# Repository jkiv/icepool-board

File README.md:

icepool-board
=============

KiCad 5 design files for the `icepool` project.

`icepool` is a FPGA cluster and development board.

Key features include,

- 16x headers for daughter boards.
- An FT2232H for USB communication and parallel FPGA flashing.
- One-to-many SPI interface for sending data from the PC to each daughter board.
- Daisy-chained SPI interface for passing data to and from the PC and each daughter board.
- A 6-pin ATX +12V power connector for use with conventional PC power supplies.

Currently, the project includes a daughter board design featuring a single [ice40hx8k-bg121](http://www.latticesemi.com/iCE40) FPGA with independent 1.2V LDO, 12MHz oscillator, and indicator LED.

## Dependencies

This project depends on the following KiCad libraries:

* [Digi-Key/digikey-kicad-library](https://github.com/Digi-Key/digikey-kicad-library)
* [jkiv/jkiv-kicad-library](https://github.com/jkiv/jkiv-kicad-library)

These repositories are set up as git submodules and can be cloned into `hardware/external/` using the following two commands:

    $ git submodule init
    $ git submodule update

## Drivers

See [jkiv/icepool-driver](https://github.com/jkiv/icepool-driver) project for a general-purpose Linux C library with Python3 bindings.

## Cores

* [jkiv/shapool-core](https://github.com/jkiv/shapool-core) - a SHA256d hashing core for cryptocurrency mining.

## Donate

Please consider supporting this project and others like it by donating:

* ☕: [ko-fi.com/jkiv_](https://ko-fi.com/jkiv_)
* ₿: `13zRrs1YDdooUN5WtfXRSDn8KnJdok4qG9`

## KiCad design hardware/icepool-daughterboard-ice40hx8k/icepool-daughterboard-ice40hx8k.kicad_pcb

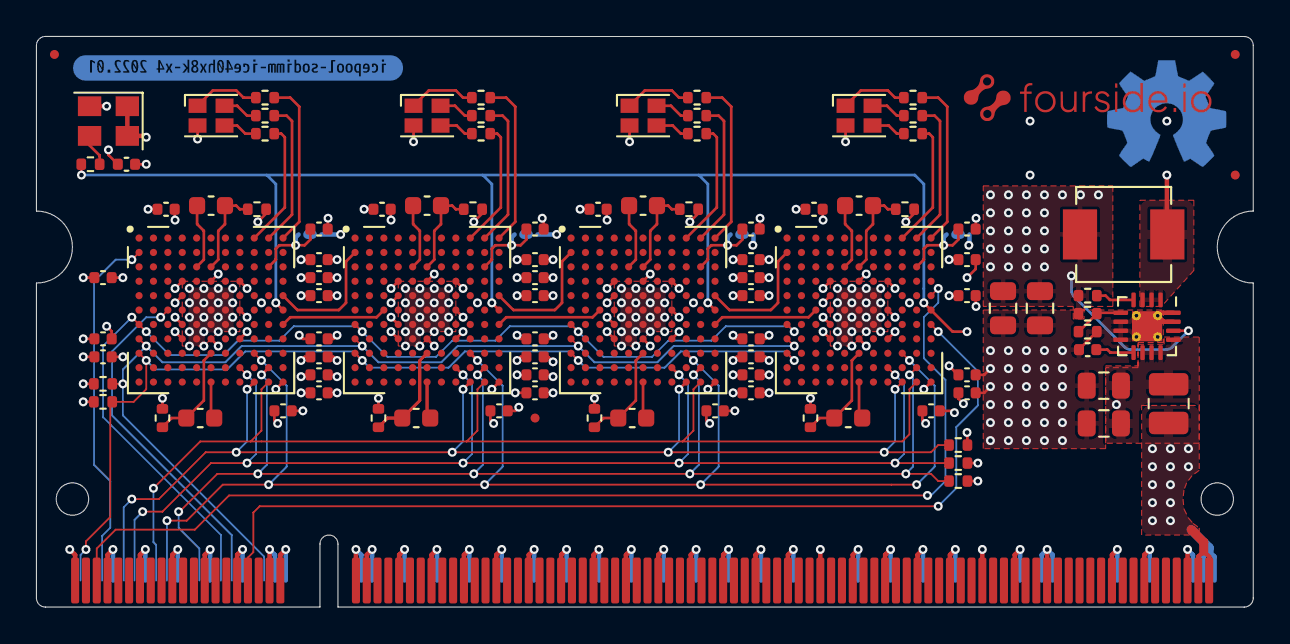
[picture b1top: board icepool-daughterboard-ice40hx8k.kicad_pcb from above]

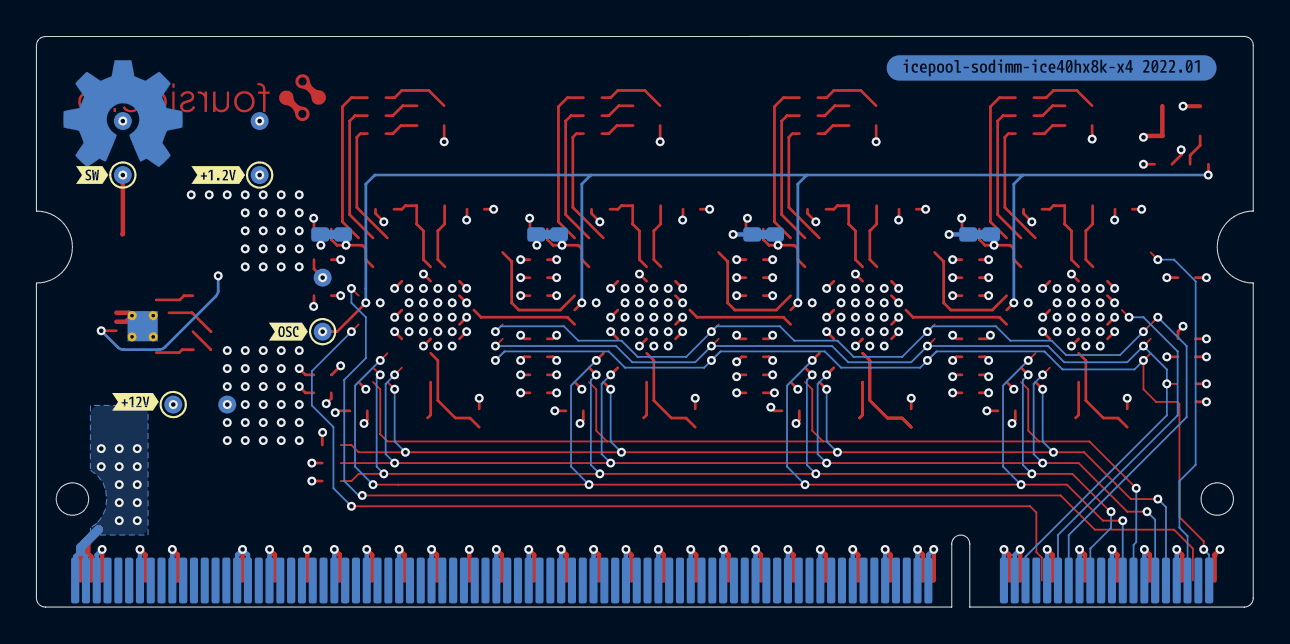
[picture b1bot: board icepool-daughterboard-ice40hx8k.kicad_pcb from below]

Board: 6 copper layers, 67.6 x 31.7 mm, 119 parts (19 on the bottom side), 73 nets.

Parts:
C1, C53: DNP; C_0805_2012Metric
C2, C4: 22u; C_0805_2012Metric
C3: 3.3n; C_0402_1005Metric
C5, C6, C7, C8, C9, C10, C11, C12, C14, C15, C17, C18, C19, C20, C21, C22, C23, C24, C26, C27, C29, C30, C31, C32, C33, C34, C35, C36, C38, C39, C41, C42, C43, C44, C45, C46, C47, C48, C50, C51: 0.1u; C_0402_1005Metric
C13, C16, C25, C28, C37, C40, C49, C52: 10u; C_0603_1608Metric
C54: 22u; C_0402_1005Metric
D1, D2, D3, D4: ACT_LED; LED_Cree-PLCC4_2x2mm_CW
FID1, FID2, FID3, FID4: Fiducial; Fiducial_0.5mm_Mask1mm
J1: SODIMM-200_Split; SODIMM-200-DDR2-PCB
JP1, JP2, JP3, JP4: CUT_2V5; J_Small_NC
L1: FB; L_1008_2520Metric
L2: 2.2u; L_Vishay_IHLP-2020
OSHW1: Logo_Open_Hardware_Small; OSHW-Symbol_6.7x6mm_Copper
R1: 100k; R_0402_1005Metric
R2: 75k; R_0402_1005Metric
R3: 150k; R_0402_1005Metric
R4: 22R; R_0402_1005Metric
R5, R6, R15, R16, R25, R26, R35, R36: 100R; R_0402_1005Metric
R7, R8, R10, R12, R14: 10k; R_0402_1005Metric
R9, R11, R13, R19, R21, R23, R29, R31, R33, R39, R41, R43: 1k; R_0402_1005Metric
TP1: SW_1v2; TestPoint_Pad_D1.0mm
TP2, TP4, TP6, TP8: GND; TestPoint_Pad_D1.0mm
TP3: +12V; TestPoint_Pad_D1.0mm
TP5: +1v2; TestPoint_Pad_D1.0mm
TP7: OSC_CORE; TestPoint_Pad_D1.0mm
U0, U1, U2, U3: iCE40HX8K-BG121(121-Ball_caBGA); BGA-121_11x11_9.0x9.0mm
U4: TPS62140; VQFN-16-1EP_3x3mm_P0.5mm_EP1.68x1.68mm_ThermalVias
X1: ASEM1-12.000MHZ; Oscillator_SMD_Abracon_ASE-4Pin_3.2x2.5mm
kibuzzard-62B88C8F: G***; kibuzzard-62B88C8F
kibuzzard-62B88CC0: G***; kibuzzard-62B88CC0
kibuzzard-62B88D1E: G***; kibuzzard-62B88D1E
kibuzzard-62B88D7B: G***; kibuzzard-62B88D7B
kibuzzard-62C46161: G***; kibuzzard-62C46161
kibuzzard-62C46174: G***; kibuzzard-62C46174

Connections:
12V_IN: J1.197, J1.198, J1.199, J1.200, L1.1
+1V2: C4.1, C6.2, C9.2, C11.2, C14.2, C18.2, C21.2, C23.2, C26.2, C30.2, C33.2, C35.2, C38.2, C42.2, C45.2, C47.2, C50.2, C53.1, L2.2, R1.1, R2.1, R5.2, R6.2, R15.2, R16.2, R25.2, R26.2, R35.2, R36.2, TP5.1, U0.D4 (VCC), U0.D8 (VCC), U0.H4 (VCC), U0.H8 (VCC), U1.D4 (VCC), U1.D8 (VCC), U1.H4 (VCC), U1.H8 (VCC), U2.D4 (VCC), U2.D8 (VCC), U2.H4 (VCC), U2.H8 (VCC), U3.D4 (VCC), U3.D8 (VCC), U3.H4 (VCC), U3.H8 (VCC), U4.14 (VOS)
+3V3: C5.2, C7.2, C10.2, C12.2, C15.2, C17.2, C19.2, C22.2, C24.2, C27.2, C29.2, C31.2, C34.2, C36.2, C39.2, C41.2, C43.2, C46.2, C48.2, C51.2, C54.2, D1.4 (A), D2.4 (A), D3.4 (A), D4.4 (A), J1.39, J1.40, J1.41, J1.42, JP1.1, JP2.1, JP3.1, JP4.1, R7.1, R8.1, R10.1, R12.1, U0.D6 (VCCIO_0), U0.E4 (VCCIO_3), U0.F8 (VCCIO_1), U0.G4 (VCCIO_3), U0.H6 (VCCIO_2), U0.L11 (VCC_SPI), U1.D6 (VCCIO_0), U1.E4 (VCCIO_3), U1.F8 (VCCIO_1), U1.G4 (VCCIO_3), U1.H6 (VCCIO_2), U1.L11 (VCC_SPI), U2.D6 (VCCIO_0), U2.E4 (VCCIO_3), U2.F8 (VCCIO_1), U2.G4 (VCCIO_3), U2.H6 (VCCIO_2), U2.L11 (VCC_SPI), U3.D6 (VCCIO_0), U3.E4 (VCCIO_3), U3.F8 (VCCIO_1), U3.G4 (VCCIO_3), U3.H6 (VCCIO_2), U3.L11 (VCC_SPI), X1.1 (EN), X1.4 (Vdd)
+12V: C1.2, C2.2, L1.2, TP3.1, U4.10 (AVIN), U4.11 (PVIN), U4.12 (PVIN), U4.13 (EN)
/CDONE: J1.12, R10.2, U0.K8 (CDONE), U1.K8 (CDONE), U3.K8 (CDONE)
/CRESET_B: J1.10, R7.2, U0.L9 (CRESET_B), U1.L9 (CRESET_B), U2.L9 (CRESET_B), U3.L9 (CRESET_B)
/OSC_CORE: R4.1, TP7.1, U0.F11 (GBIN3/IOR_140/PIO1_11), U1.F11 (GBIN3/IOR_140/PIO1_11), U2.F11 (GBIN3/IOR_140/PIO1_11), U3.F11 (GBIN3/IOR_140/PIO1_11)
/SCK0: J1.16, U0.L10 (SCK/IOB_107/PIO2_21), U1.L10 (SCK/IOB_107/PIO2_21), U2.L10 (SCK/IOB_107/PIO2_21), U3.L10 (SCK/IOB_107/PIO2_21)
/SCK1: J1.28, U0.G1 (GBIN6/IOL_14A/PIO3_16), U1.G1 (GBIN6/IOL_14A/PIO3_16), U2.G1 (GBIN6/IOL_14A/PIO3_16), U3.G1 (GBIN6/IOL_14A/PIO3_16)
/SDI0: J1.18, U0.J9 (SDI/IOB_106/PIO2_20), U1.J9 (SDI/IOB_106/PIO2_20), U2.J9 (SDI/IOB_106/PIO2_20), U3.J9 (SDI/IOB_106/PIO2_20)
/SDI1: J1.30, U0.F3 (GBIN7/IOL_13B/PIO3_15)
/SDO1: J1.33, U3.G11 (IOR_129/PIO1_08)
/SW_1v2: L2.1, TP1.1, U4.1 (SW), U4.2 (SW), U4.3 (SW)
/ice40-hx8k 1/GNDPLL0: C25.2, U1.L6 (GNDPLL0)
/ice40-hx8k 1/GNDPLL1: C28.2, U1.C5 (GNDPLL1)
/ice40-hx8k 1/SDI1: U0.G11 (IOR_129/PIO1_08), U1.F3 (GBIN7/IOL_13B/PIO3_15)
/ice40-hx8k 1/SDO1: U1.G11 (IOR_129/PIO1_08), U2.F3 (GBIN7/IOL_13B/PIO3_15)
/ice40-hx8k 1/VCCPLL0: C25.1, R15.1, U1.J6 (VCCPLL0)
/ice40-hx8k 1/VCCPLL1: C28.1, R16.1, U1.C6 (VCCPLL1)
/ice40-hx8k 1/VPP_2V5: C20.2, JP2.2, U1.C10 (VPP_2V5)
/ice40-hx8k 1/~ACT_B: R23.1, U1.A9 (IOT_178/PIO0_05)
/ice40-hx8k 1/~ACT_G: R21.1, U1.A10 (IOT_170/PIO0_01)
/ice40-hx8k 1/~ACT_R: R19.1, U1.A11 (IOT_168/PIO0_00)
/ice40-hx8k 1/~READY_IN: U1.E11 (IOR_148/PIO1_16), U2.B1 (IOL_2A/PIO3_00)
/ice40-hx8k 1/~READY_OUT: U0.E11 (IOR_148/PIO1_16), U1.B1 (IOL_2A/PIO3_00)
/ice40-hx8k 2/GNDPLL0: C37.2, U2.L6 (GNDPLL0)
/ice40-hx8k 2/GNDPLL1: C40.2, U2.C5 (GNDPLL1)
/ice40-hx8k 2/SDO1: U2.G11 (IOR_129/PIO1_08), U3.F3 (GBIN7/IOL_13B/PIO3_15)
/ice40-hx8k 2/VCCPLL0: C37.1, R25.1, U2.J6 (VCCPLL0)
/ice40-hx8k 2/VCCPLL1: C40.1, R26.1, U2.C6 (VCCPLL1)
/ice40-hx8k 2/VPP_2V5: C32.2, JP3.2, U2.C10 (VPP_2V5)
/ice40-hx8k 2/~ACT_B: R33.1, U2.A9 (IOT_178/PIO0_05)
/ice40-hx8k 2/~ACT_G: R31.1, U2.A10 (IOT_170/PIO0_01)
/ice40-hx8k 2/~ACT_R: R29.1, U2.A11 (IOT_168/PIO0_00)
/ice40-hx8k 2/~READY_IN: U2.E11 (IOR_148/PIO1_16), U3.B1 (IOL_2A/PIO3_00)
/ice40-hx8k 3/GNDPLL0: C49.2, U3.L6 (GNDPLL0)
/ice40-hx8k 3/GNDPLL1: C52.2, U3.C5 (GNDPLL1)
/ice40-hx8k 3/VCCPLL0: C49.1, R35.1, U3.J6 (VCCPLL0)
/ice40-hx8k 3/VCCPLL1: C52.1, R36.1, U3.C6 (VCCPLL1)
/ice40-hx8k 3/VPP_2V5: C44.2, JP4.2, U3.C10 (VPP_2V5)
/ice40-hx8k 3/~ACT_B: R43.1, U3.A9 (IOT_178/PIO0_05)
/ice40-hx8k 3/~ACT_G: R41.1, U3.A10 (IOT_170/PIO0_01)
/ice40-hx8k 3/~ACT_R: R39.1, U3.A11 (IOT_168/PIO0_00)
/ice40hx8k 0/GNDPLL0: C13.2, U0.L6 (GNDPLL0)
/ice40hx8k 0/GNDPLL1: C16.2, U0.C5 (GNDPLL1)
/ice40hx8k 0/VCCPLL0: C13.1, R5.1, U0.J6 (VCCPLL0)
/ice40hx8k 0/VCCPLL1: C16.1, R6.1, U0.C6 (VCCPLL1)
/ice40hx8k 0/VPP_2V5: C8.2, JP1.2, U0.C10 (VPP_2V5)
/ice40hx8k 0/~ACT_B: R13.1, U0.A9 (IOT_178/PIO0_05)
/ice40hx8k 0/~ACT_G: R11.1, U0.A10 (IOT_170/PIO0_01)
/ice40hx8k 0/~ACT_R: R9.1, U0.A11 (IOT_168/PIO0_00)
/~CS0: J1.24, R14.2, U0.K10 (SS/IOB_108/PIO2_22), U1.K10 (SS/IOB_108/PIO2_22), U2.K10 (SS/IOB_108/PIO2_22), U3.K10 (SS/IOB_108/PIO2_22)
/~CS1: J1.36, R12.2, U0.H1 (IOL_18A/PIO3_20), U1.H1 (IOL_18A/PIO3_20), U2.H1 (IOL_18A/PIO3_20), U3.H1 (IOL_18A/PIO3_20)
/~READY_IN: J1.5, U3.E11 (IOR_148/PIO1_16)
/~READY_OUT: J1.6, U0.B1 (IOL_2A/PIO3_00)
/~RESET: J1.2, R8.2, U0.J1 (IOL_23A/PIO3_22), U1.J1 (IOL_23A/PIO3_22), U2.J1 (IOL_23A/PIO3_22), U3.J1 (IOL_23A/PIO3_22)
GND: C1.1, C2.1, C3.2, C4.2, C5.1, C6.1, C7.1, C8.1, C9.1, C10.1, C11.1, C12.1, C14.1, C15.1, C17.1, C18.1, C19.1, C20.1, C21.1, C22.1, C23.1, C24.1, C26.1, C27.1, C29.1, C30.1, C31.1, C32.1, C33.1, C34.1, C35.1, C36.1, C38.1, C39.1, C41.1, C42.1, C43.1, C44.1, C45.1, C46.1, C47.1, C48.1, C50.1, C51.1, C53.2, C54.1, J1.1, J1.7, J1.8, J1.13, J1.14, J1.19, J1.20, J1.25, J1.26, J1.31, J1.32, J1.37, J1.38, J1.43, J1.44, J1.49, J1.50, J1.55, J1.56, J1.61, J1.62, J1.67, J1.68, J1.73, J1.74, J1.79, J1.80, J1.85, J1.86, J1.91, J1.92, J1.97, J1.98, J1.103, J1.104, J1.109, J1.110, J1.115, J1.116, J1.121, J1.122, J1.127, J1.133, J1.134, J1.139, J1.140, J1.145, J1.146, J1.151, J1.152, J1.157, J1.163, J1.164, J1.168, J1.169, J1.170, J1.181, J1.182, J1.187, J1.188, J1.195, J1.196, R3.2, R14.1, TP2.1, TP4.1, TP6.1, TP8.1, U0.E5 (GND), U0.E6 (GND), U0.E7 (GND), U0.F5 (GND), U0.F6 (GND), U0.F7 (GND), U0.G5 (GND), U0.G6 (GND), U0.G7 (GND), U0.H5 (GND), U1.E5 (GND), U1.E6 (GND), U1.E7 (GND), U1.F5 (GND), U1.F6 (GND), U1.F7 (GND), U1.G5 (GND), U1.G6 (GND), U1.G7 (GND), U1.H5 (GND), U2.E5 (GND), U2.E6 (GND), U2.E7 (GND), U2.F5 (GND), U2.F6 (GND), U2.F7 (GND), U2.G5 (GND), U2.G6 (GND), U2.G7 (GND), U2.H5 (GND), U3.E5 (GND), U3.E6 (GND), U3.E7 (GND), U3.F5 (GND), U3.F6 (GND), U3.F7 (GND), U3.G5 (GND), U3.G6 (GND), U3.G7 (GND), U3.H5 (GND), U4.6 (AGND), U4.7 (FSW), U4.8 (DEF), U4.15 (PGND), U4.16 (PGND), U4.17 (EP), X1.2 (GND)
unnamed: C3.1, U4.9 (SS/TR)
unnamed: D1.1 (RK), R9.2
unnamed: D1.2 (GK), R11.2
unnamed: D1.3 (BK), R13.2
unnamed: D2.1 (RK), R19.2
unnamed: D2.2 (GK), R21.2
unnamed: D2.3 (BK), R23.2
unnamed: D3.1 (RK), R29.2
unnamed: D3.2 (GK), R31.2
unnamed: D3.3 (BK), R33.2
unnamed: D4.1 (RK), R39.2
unnamed: D4.2 (GK), R41.2
unnamed: D4.3 (BK), R43.2
unnamed: R1.2, U4.4 (PG)
unnamed: R2.2, R3.1, U4.5 (FB)
unnamed: R4.2, X1.3 (OUT)

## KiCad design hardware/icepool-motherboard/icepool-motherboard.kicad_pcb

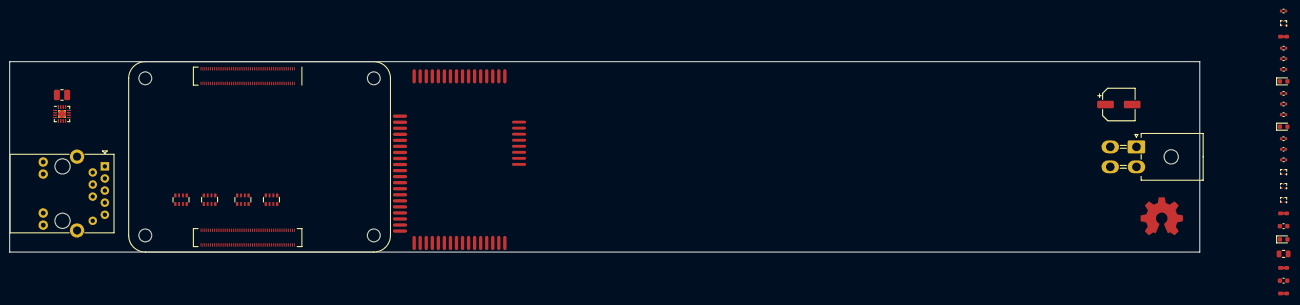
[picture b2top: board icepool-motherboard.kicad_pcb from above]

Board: 2 copper layers, 250.0 x 40.0 mm, 40 parts (1 on the bottom side), 57 nets, no tracks yet.

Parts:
C1: 22u; C_0805_2012Metric
C2: 47u; CP_Elec_6.3x5.9
C3: 10u; C_0603_1608Metric
C4: 3.3n; C_0402_1005Metric
C5: 22u; C_0603_1608Metric
D1: PI_ACT; LED_0603_1608Metric
D3: 5V; LED_0603_1608Metric
D4: 3v3; LED_0603_1608Metric
D6, D7, D8, D9: TPD2EUSB30DRTR; SOT-3
J1: microSD; microSD_HC_Molex_104031-0811
J2: PWR; Molex_Mini-Fit_Jr_5569-04A2_2x02_P4.20mm_Horizontal
J3: Abracon_ARJM11-502; RJ45_Abracon_ARJP11A-MA_Horizontal
J4: S; PinHeader_1x20_P1.27mm_Vertical
J5: E; PinHeader_1x16_P1.27mm_Vertical
J6: W; PinHeader_1x16_P1.27mm_Vertical
J7: N; PinHeader_1x08_P1.27mm_Vertical
JP1, JP4: ~WL_nDisable; J_Small_NC
JP2: ~BT_nDisable; J_Small_NC
JP3: EEPROM_nWP; J_Small_NC
L2: 2.2u; L_1008_2520Metric
OSHW1: Logo_Open_Hardware_Small; OSHW-Symbol_8.9x8mm_Copper
R1, R3, R4, R8: 220R; R_0402_1005Metric
R2, R10, R11: 1k0; R_0402_1005Metric
R6: 330R; R_0402_1005Metric
R12: 100k; R_0402_1005Metric
RN1, RN2, RN3, RN4: 22R; R_Array_Convex_4x0603
U1: CM4; Raspberry-Pi-4-Compute-Module
U2: TPS62140; VQFN-16-1EP_3x3mm_P0.5mm_EP1.68x1.68mm_ThermalVias

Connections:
+1V8: U1.88, U1.90
+3V3: C1.1, D1.2, D4.2, J1.4, J3.11, J3.13, JP4.2, U1.78, U1.84, U1.86
+5V: C5.1, D3.2, L2.2, R12.1, U1.77, U1.79, U1.81, U1.83, U1.85, U1.87, U2.14
/5V_SW: L2.1, U2.1, U2.2, U2.3
/CIPO1: RN4.3, U1.26
/COPI0: RN1.3, RN3.3, U1.44
/COPI1: RN2.2, U1.27
/ETH_TD1+: D6.1, J3.1, U1.12
/ETH_TD1-: D6.2, J3.2, U1.10
/ETH_TD2+: D7.1, J3.3, U1.4
/ETH_TD2-: D7.2, J3.4, U1.6
/ETH_TD3+: D8.1, J3.7, U1.11
/ETH_TD3-: D8.2, U1.9
/ETH_TD4+: D9.1, J3.9, U1.3
/ETH_TD4-: D9.2, J3.10, U1.5
/FPGA_CDONE: J4.16, U1.46
/FPGA_CRESETB: RN2.4, U1.37
/FPGA_~READY~: J4.2, RN4.1, U1.58
/FPGA_~RESET~: RN1.4, RN3.4, U1.56
/Nodes/COPI0: J4.12, RN1.6
/Nodes/COPI1: J4.6, RN2.7
/Nodes/CRESETB: J4.18, RN2.5
/Nodes/SCK0: J4.10, RN1.8
/Nodes/SCK1: J4.4, RN2.8
/Nodes/~CS0: J4.14, RN1.7
/Nodes/~CS1: J4.8, RN2.6
/Nodes/~RESET: J4.20, RN1.5
/PI_GLOBAL_EN: R4.2, U1.99
/PI_LED_nACT: R1.2, U1.21
/SCK0: RN1.1, RN3.1, U1.38
/SCK1: RN2.1, U1.25
/SD_CLK: J1.5, U1.57
/SD_CMD: J1.3, U1.62
/SD_DAT0: J1.7, U1.63
/SD_DAT1: J1.8, U1.67
/SD_DAT2: J1.1, U1.69
/SD_DAT3: J1.2, U1.61
/~CS0: RN1.2, RN3.2, U1.39
/~CS1: RN2.3, U1.49
/~ETH_LEDL: R11.2, U1.17
/~ETH_LEDR: R10.2, U1.19
GND: C1.2, C2.2, C3.1, C4.2, C5.2, D6.3, D7.3, D8.3, D9.3, J1.6, J1.9, J4.1, J4.3, J4.5, J4.7, J4.9, J4.11, J4.13, J4.15, J4.17, J4.19, J5.1, J5.2, J5.3, J5.4, J5.5, J5.6, J5.7, J5.8, J5.9, J5.11, J5.13, J5.15, J6.1, J6.2, J6.3, J6.4, J6.5, J6.6, J6.7, J6.8, J6.9, J6.10, J6.11, J6.12, J7.2, J7.4, J7.6, J7.8, JP1.1, JP2.1, JP3.1, R2.1, R6.2, R8.2, RN3.5, RN3.6, RN3.7, RN3.8, RN4.5, RN4.6, RN4.7, RN4.8, U1.1, U1.2, U1.7, U1.8, U1.13, U1.14, U1.22, U1.23, U1.32, U1.33, U1.42, U1.43, U1.52, U1.53, U1.59, U1.60, U1.65, U1.66, U1.71, U1.74, U1.98, U1.107, U1.108, U1.113, U1.114, U1.119, U1.120, U1.125, U1.126, U1.131, U1.132, U1.137, U1.138, U1.144, U1.150, U1.155, U1.156, U1.161, U1.162, U1.167, U1.168, U1.173, U1.174, U1.179, U1.180, U1.185, U1.186, U1.191, U1.192, U1.197, U1.198, U2.5, U2.6, U2.7, U2.8, U2.15, U2.16, U2.17
unnamed: C4.1, U2.9
unnamed: D1.1, R1.1
unnamed: D3.1, R6.1
unnamed: D4.1, R8.1
unnamed: J2.1, J2.2
unnamed: J2.3, J2.4
unnamed: J3.5, J3.6
unnamed: J3.12, R11.1
unnamed: J3.14, R10.1
unnamed: JP1.2, U1.89
unnamed: JP2.2, U1.91
unnamed: JP3.2, U1.20
unnamed: JP4.1, U1.73
unnamed: R12.2, U2.4
VBUS: C2.1, C3.2, J6.13, J6.14, J6.15, J6.16, U2.10, U2.11, U2.12, U2.13

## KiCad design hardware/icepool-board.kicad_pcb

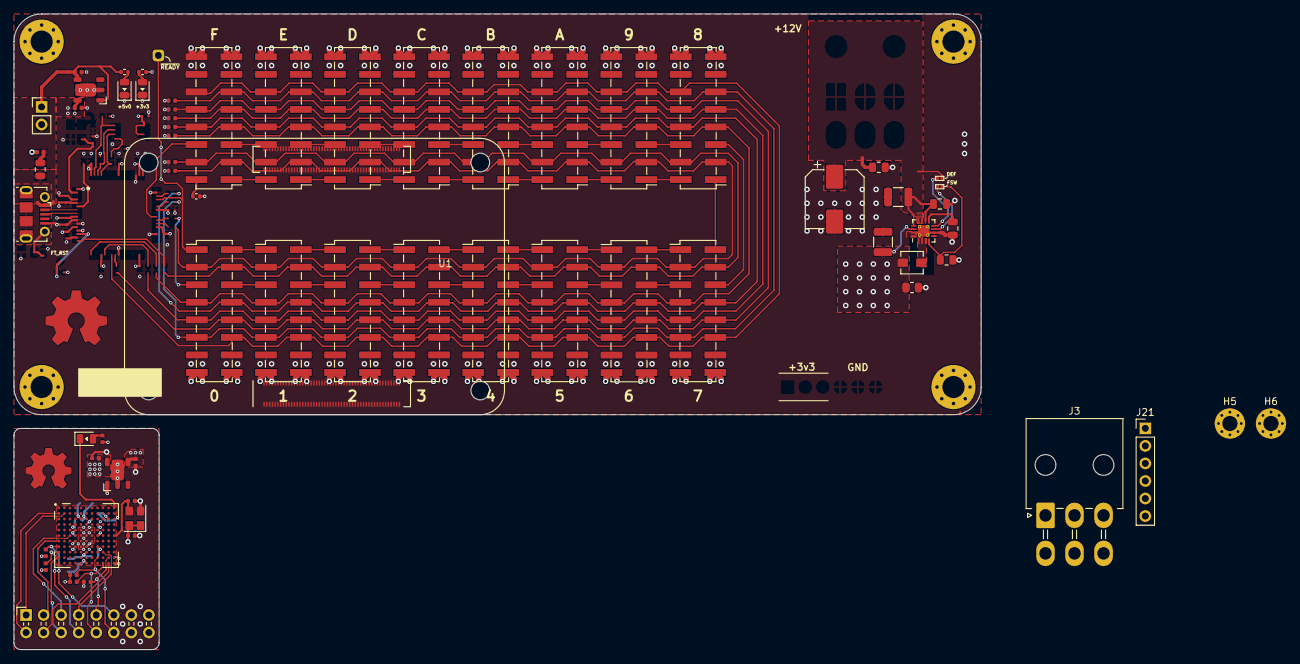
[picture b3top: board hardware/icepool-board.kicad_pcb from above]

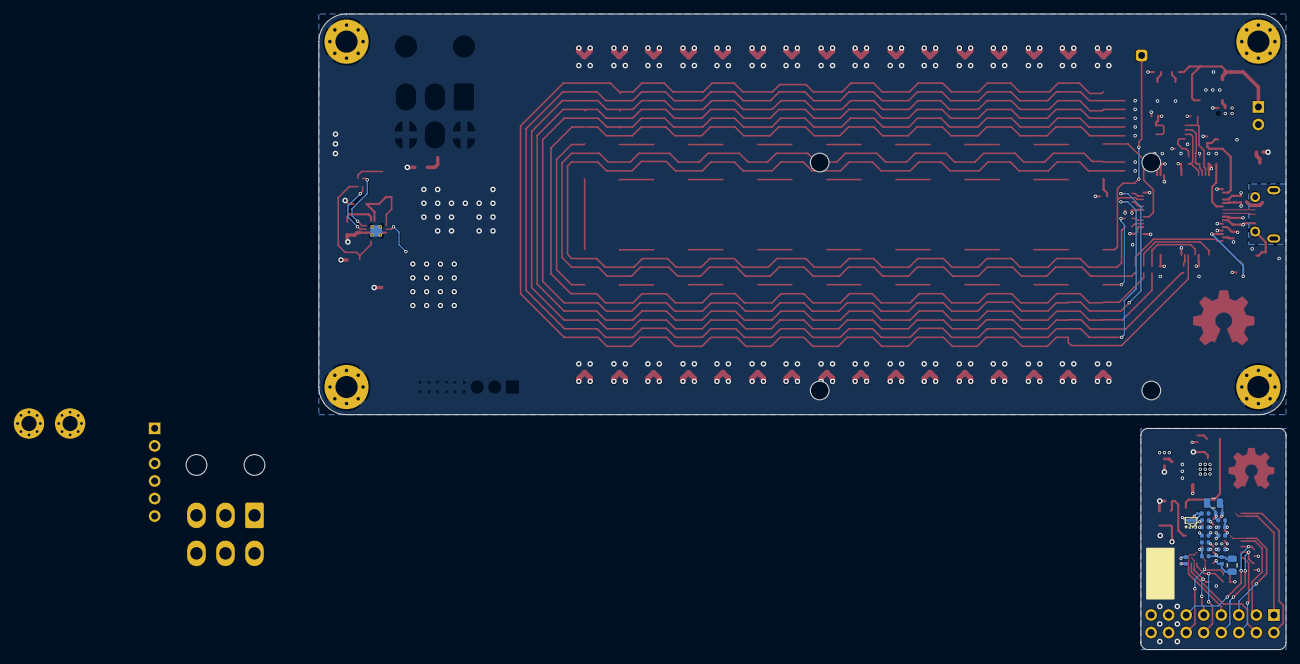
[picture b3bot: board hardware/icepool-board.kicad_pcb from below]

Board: 4 copper layers, 140.0 x 92.0 mm, 91 parts (17 on the bottom side), 76 nets.

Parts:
C7, C11, C12, C21, C22: 4.7u; C_0402_1005Metric
C15: 47u; CP_Elec_8x10
C16, C23, C24, C25, C26, C27, C28, C29, C30, C32, C33, C34, C36: 0.1u; C_0402_1005Metric
C17: DNP; C_0402_1005Metric
C31, C35: 10u; C_0805_2012Metric
C37: 10u; C_1210_3225Metric
C38: 3.3u; C_0805_2012Metric
C39: 0.1u; C_0805_2012Metric
C41: 22u; C_1210_3225Metric
D1: VBUS_LED; LED_0805_2012Metric
D2: LED_IND; LED_0805_2012Metric
D3: PWRLED; LED_0805_2012Metric
FB1: FB; L_0805_2012Metric
H1, H2, H3, H4: M3_PHT; MountingHole_3.2mm_M3_Pad_Via
H5, H6: MountingHole_Pad; MountingHole_2.2mm_M2_Pad_Via
J1: USB_B_Micro; USB_Micro-B_Molex-105017-0001
J2: USE_VBUS_5V; PinHeader_1x02_P2.54mm_Vertical
J3: PCIe_6pin; Molex_Mini-Fit_Jr_5569-06A2_2x03_P4.20mm_Horizontal
J4, J5, J6, J7, J8, J9, J10, J11, J12, J13, J14, J15, J16, J17, J18, J19: Conn_02x08_Odd_Even; PinHeader_2x08_P2.54mm_Vertical_SMD
J20: Conn_02x08_Odd_Even; PinSocket_2x08_P2.54mm_Horizontal
J21: PWR_ALT; PinHeader_1x06_P2.54mm_Vertical
J22: ~READY; PinHeader_1x01_P2.54mm_Vertical
JP1: CUT_2V5; SolderJumper-2_P1.3mm_Bridged_Pad1.0x1.5mm
JP2, JP3: FSW; J_NO_0201_0603Metric
L1: 2.2u; L_Vishay_IHLP-1212
OSHW1: Logo_Open_Hardware_Small; OSHW-Symbol_6.7x6mm_Copper
OSHW2: Logo_Open_Hardware_Small; OSHW-Symbol_8.9x8mm_Copper
R1, R25, R36: 4k7; R_0402_1005Metric
R10, R24, R26, R27, R28, R29, R30: DNP; R_0402_1005Metric
R14: 1k; R_0402_1005Metric
R15, R16: 100R; R_0402_1005Metric
R17, R18, R19, R20, R31: 10k; R_0402_1005Metric
R21, R22, R23: 100k; R_0805_2012Metric
U1: Compute_Module_4_Connectors; Raspberry-Pi-4-Compute-Module
U2, U7: AP7361C_SOT-89-5; SOT89-5
U3: TPS62132; VQFN-16-1EP_3x3mm_P0.5mm_EP1.68x1.68mm_ThermalVias
U8: iCE40HX8K-BG121(121-Ball_caBGA); BGA-121_11x11_9.0x9.0mm
X2: ASEM1-12.000MHZ; Oscillator_SMD_Abracon_ASE-4Pin_3.2x2.5mm

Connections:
+1V2: C22.1, C24.2, C27.2, C29.2, C33.2, R15.2, R16.2, U7.5, U8.D4, U8.D8, U8.H4, U8.H8
+3V3: C12.1, C16.2, C21.1, C23.2, C25.2, C28.2, C30.2, C34.2, C41.1, J4.15, J4.16, J5.15, J5.16, J6.15, J6.16, J7.15, J7.16, J8.15, J8.16, J9.15, J9.16, J10.15, J10.16, J11.15, J11.16, J12.15, J12.16, J13.15, J13.16, J14.15, J14.16, J15.15, J15.16, J16.15, J16.16, J17.15, J17.16, J18.15, J18.16, J19.15, J19.16, J20.15, J20.16, J21.1, J21.2, J21.3, JP1.1, L1.2, R14.2, R18.1, R19.1, R20.1, R22.1, R23.1, R25.1, R31.1, U2.5, U3.14, U7.1, U7.4, U8.D6, U8.E4, U8.F8, U8.G4, U8.H6, U8.L11, X2.1, X2.4
+5V: C11.1, J2.1, R1.1, U2.1, U2.4
+12V: C15.1, C37.1, C39.1, J3.1, J3.2, J3.3, JP3.1, R21.1, U3.10, U3.11, U3.12, U3.13
/ice40hx8k-daughter-board/CDONE: J20.12, R20.2, U8.K8
/ice40hx8k-daughter-board/CLK_FPGA: C17.2, U8.F11, X2.3
/ice40hx8k-daughter-board/CRESET_B: J20.10, R18.2, U8.L9
/ice40hx8k-daughter-board/SCK0: J20.4, U8.L10
/ice40hx8k-daughter-board/SCK1: J20.3, U8.G1
/ice40hx8k-daughter-board/SDI0: J20.7, U8.J9
/ice40hx8k-daughter-board/SDI1: J20.5, U8.F3
/ice40hx8k-daughter-board/SDO1: J20.6, U8.K1
/ice40hx8k-daughter-board/ice40-hx8k-bg121/GNDPLL0: C31.2, C32.2, U8.L6
/ice40hx8k-daughter-board/ice40-hx8k-bg121/GNDPLL1: C35.2, C36.2, U8.C5
/ice40hx8k-daughter-board/ice40-hx8k-bg121/VCCPLL0: C31.1, C32.1, R15.1, U8.J6
/ice40hx8k-daughter-board/ice40-hx8k-bg121/VCCPLL1: C35.1, C36.1, R16.1, U8.C6
/ice40hx8k-daughter-board/ice40-hx8k-bg121/VPP_2V5: C26.2, JP1.2, U8.C10
/ice40hx8k-daughter-board/~CS0: J20.9, R17.2, U8.K10
/ice40hx8k-daughter-board/~CS1: J20.11, R31.2, U8.H1
/ice40hx8k-daughter-board/~LED: D2.1, U8.A11
/ice40hx8k-daughter-board/~READY_IN: J20.2, U8.B1
/ice40hx8k-daughter-board/~READY_OUT: J20.1, U8.B2
/ice40hx8k-daughter-board/~RESET: J20.8, R19.2, U8.J1
/icepool-motherboard/12V-3.3V Buck/DEF: JP3.2, U3.8
/icepool-motherboard/12V-3.3V Buck/FSW: JP2.2, U3.7
/icepool-motherboard/12V-3.3V Buck/PG: JP2.1, R22.2, U3.4
/icepool-motherboard/12V-3.3V Buck/SW: L1.1, U3.1, U3.2, U3.3
/icepool-motherboard/CDONE: J4.12, J5.12, J6.12, J7.12, J8.12, J9.12, J10.12, J11.12, J12.12, J13.12, J14.12, J15.12, J16.12, J17.12, J18.12, J19.12
/icepool-motherboard/COPI0: J4.7, J5.7, J6.7, J7.7, J8.7, J9.7, J10.7, J11.7, J12.7, J13.7, J14.7, J15.7, J16.7, J17.7, J18.7, J19.7, R24.2
/icepool-motherboard/CRESET_B: J4.10, J5.10, J6.10, J7.10, J8.10, J9.10, J10.10, J11.10, J12.10, J13.10, J14.10, J15.10, J16.10, J17.10, J18.10, J19.10, R30.2
/icepool-motherboard/SCK0: J4.4, J5.4, J6.4, J7.4, J8.4, J9.4, J10.4, J11.4, J12.4, J13.4, J14.4, J15.4, J16.4, J17.4, J18.4, J19.4, R10.2
/icepool-motherboard/SCK1: J4.3, J5.3, J6.3, J7.3, J8.3, J9.3, J10.3, J11.3, J12.3, J13.3, J14.3, J15.3, J16.3, J17.3, J18.3, J19.3, R27.2
/icepool-motherboard/SDO1_0: J4.6, J5.5
/icepool-motherboard/SDO1_1: J5.6, J6.5
/icepool-motherboard/SDO1_2: J6.6, J7.5
/icepool-motherboard/SDO1_3: J7.6, J8.5
/icepool-motherboard/SDO1_4: J8.6, J9.5
/icepool-motherboard/SDO1_5: J9.6, J10.5
/icepool-motherboard/SDO1_6: J10.6, J11.5
/icepool-motherboard/SDO1_7: J11.6, J12.5
/icepool-motherboard/SDO1_8: J12.6, J13.5
/icepool-motherboard/SDO1_9: J13.6, J14.5
/icepool-motherboard/SDO1_10: J14.6, J15.5
/icepool-motherboard/SDO1_11: J15.6, J16.5
/icepool-motherboard/SDO1_12: J16.6, J17.5
/icepool-motherboard/SDO1_13: J17.6, J18.5
/icepool-motherboard/SDO1_14: J18.6, J19.5
/icepool-motherboard/USB_D+: J1.3, U1.105
/icepool-motherboard/USB_D-: J1.2, U1.103
/icepool-motherboard/VBUS: C7.1, FB1.1, J2.2
/icepool-motherboard/~CS0: J4.9, J5.9, J6.9, J7.9, J8.9, J9.9, J10.9, J11.9, J12.9, J13.9, J14.9, J15.9, J16.9, J17.9, J18.9, J19.9, R26.2
/icepool-motherboard/~CS1: J4.11, J5.11, J6.11, J7.11, J8.11, J9.11, J10.11, J11.11, J12.11, J13.11, J14.11, J15.11, J16.11, J17.11, J18.11, J19.11, R28.2
/icepool-motherboard/~READY: J4.1, J22.1
/icepool-motherboard/~READY_0: J4.2, J5.1
/icepool-motherboard/~READY_1: J5.2, J6.1
/icepool-motherboard/~READY_2: J6.2, J7.1
/icepool-motherboard/~READY_3: J7.2, J8.1
/icepool-motherboard/~READY_4: J8.2, J9.1
/icepool-motherboard/~READY_5: J9.2, J10.1
/icepool-motherboard/~READY_6: J10.2, J11.1
/icepool-motherboard/~READY_7: J11.2, J12.1
/icepool-motherboard/~READY_8: J12.2, J13.1
/icepool-motherboard/~READY_9: J13.2, J14.1
/icepool-motherboard/~READY_10: J14.2, J15.1
/icepool-motherboard/~READY_11: J15.2, J16.1
/icepool-motherboard/~READY_12: J16.2, J17.1
/icepool-motherboard/~READY_13: J17.2, J18.1
/icepool-motherboard/~READY_14: J18.2, J19.1
/icepool-motherboard/~READY_15: J19.2, R36.2
/icepool-motherboard/~RESET: J4.8, J5.8, J6.8, J7.8, J8.8, J9.8, J10.8, J11.8, J12.8, J13.8, J14.8, J15.8, J16.8, J17.8, J18.8, J19.8, R29.2
GND: C7.2, C11.2, C12.2, C15.2, C16.1, C17.1, C21.2, C22.2, C23.1, C24.1, C25.1, C26.1, C27.1, C28.1, C29.1, C30.1, C33.1, C34.1, C37.2, C38.2, C39.2, C41.2, D1.1, D3.1, H1.1, H2.1, H3.1, H4.1, H5.1, H6.1, J1.5, J3.4, J3.6, J4.13, J4.14, J5.13, J5.14, J6.13, J6.14, J7.13, J7.14, J8.13, J8.14, J9.13, J9.14, J10.13, J10.14, J11.13, J11.14, J12.13, J12.14, J13.13, J13.14, J14.13, J14.14, J15.13, J15.14, J16.13, J16.14, J17.13, J17.14, J18.13, J18.14, J19.13, J19.14, J20.13, J20.14, J21.4, J21.5, J21.6, R10.1, R17.1, R21.2, R23.2, R24.1, R26.1, R27.1, R28.1, R29.1, R30.1, R36.1, U1.1, U1.2, U1.7, U1.8, U1.13, U1.14, U1.22, U1.23, U1.32, U1.33, U1.42, U1.43, U1.52, U1.53, U1.59, U1.60, U1.65, U1.66, U1.71, U1.74, U1.98, U1.107, U1.108, U1.113, U1.114, U1.119, U1.120, U1.125, U1.126, U1.131, U1.132, U1.137, U1.138, U1.144, U1.150, U1.155, U1.156, U1.161, U1.162, U1.167, U1.168, U1.173, U1.174, U1.179, U1.180, U1.185, U1.186, U1.191, U1.192, U1.197, U1.198, U2.2, U3.5, U3.6, U3.15, U3.16, U3.17, U7.2, U8.E5, U8.E6, U8.E7, U8.F5, U8.F6, U8.F7, U8.G5, U8.G6, U8.G7, U8.H5, X2.2
unnamed: C38.1, U3.9
unnamed: D1.2, R1.2
unnamed: D2.2, R14.1
unnamed: D3.2, R25.2
unnamed: FB1.2, J1.1

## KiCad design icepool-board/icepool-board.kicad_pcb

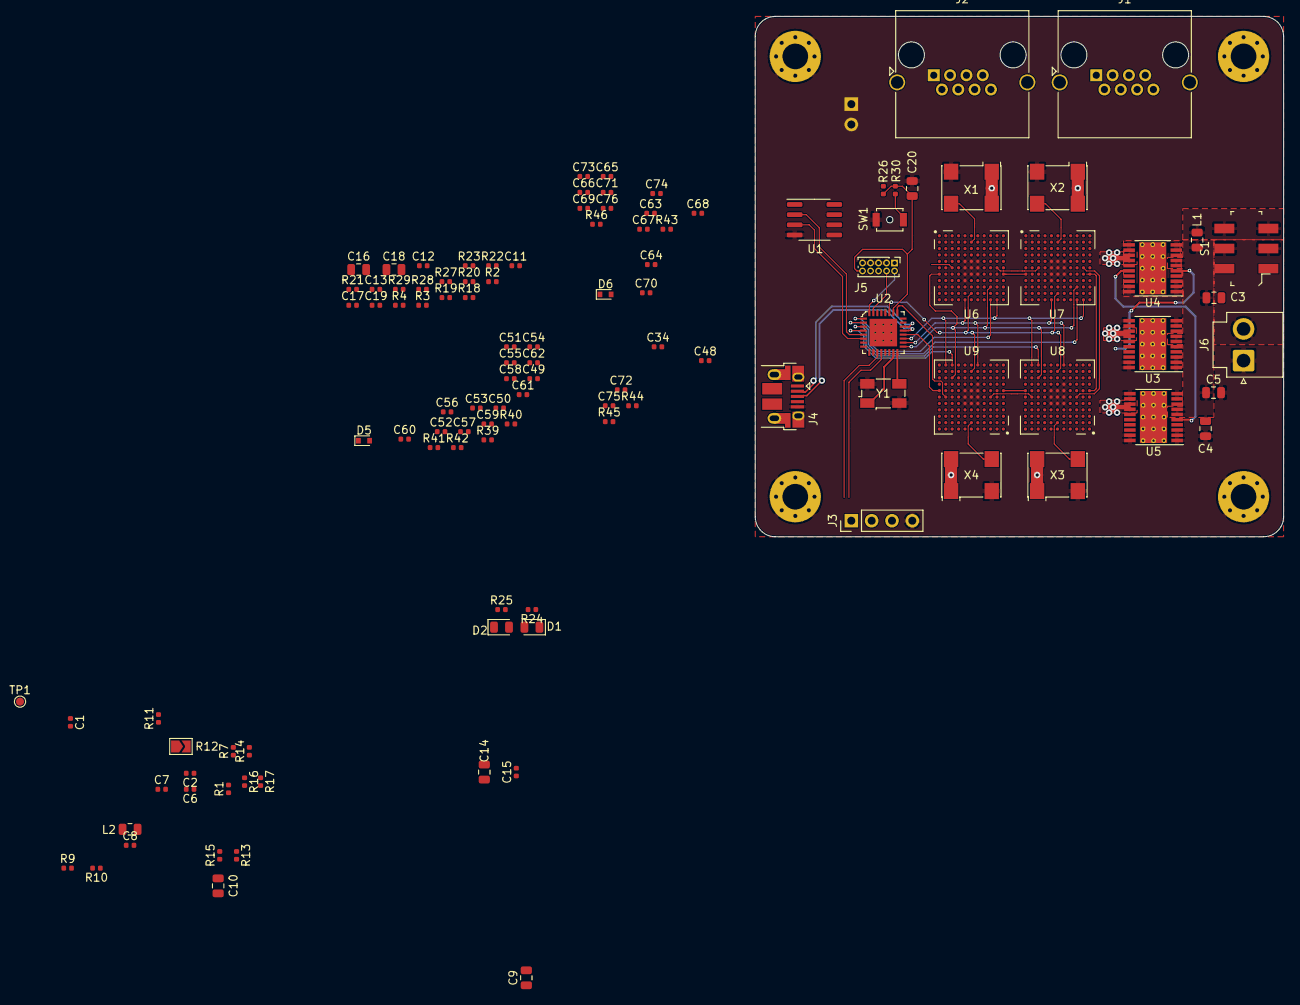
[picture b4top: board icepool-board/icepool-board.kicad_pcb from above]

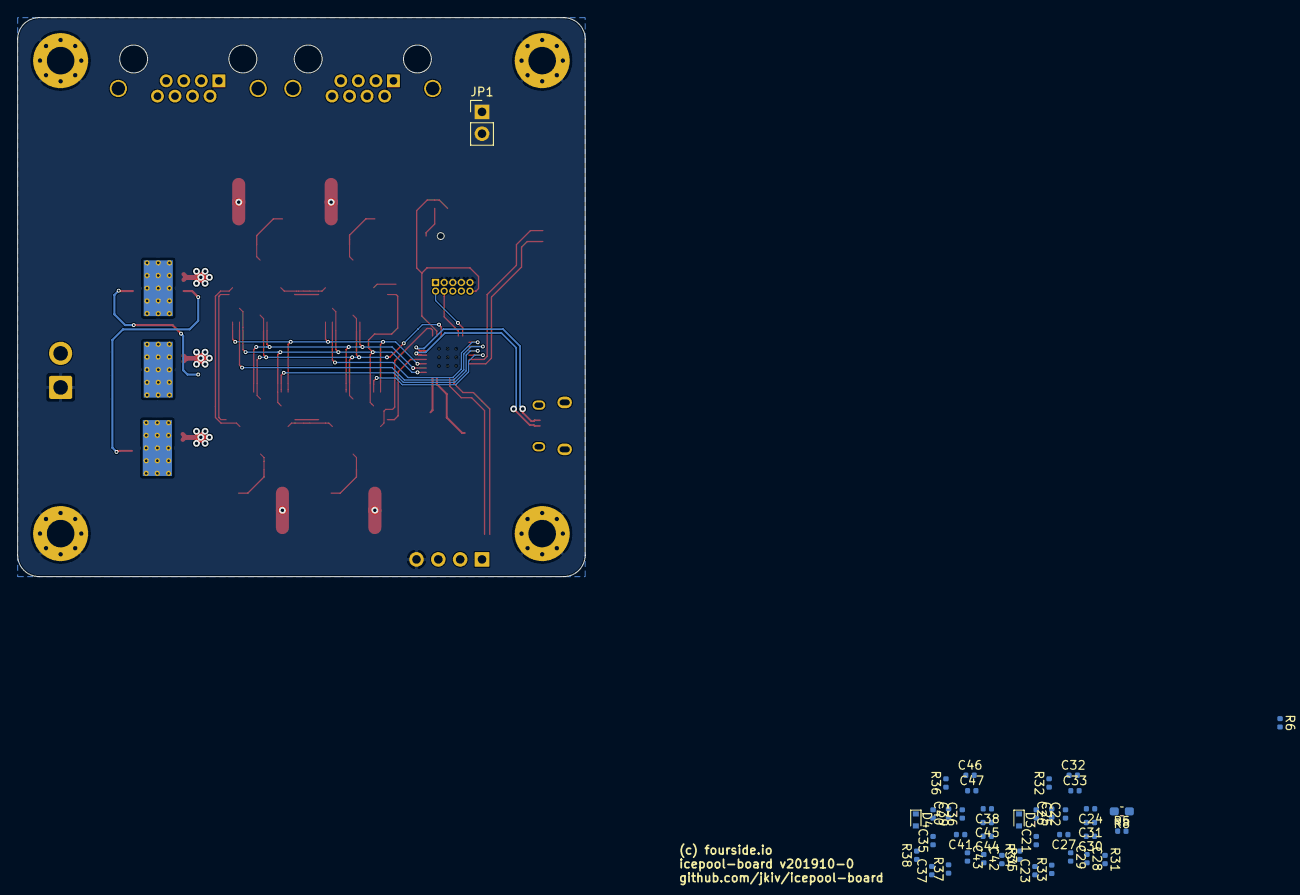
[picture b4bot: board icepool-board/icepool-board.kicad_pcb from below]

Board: 4 copper layers, 66.0 x 65.0 mm, 158 parts (40 on the bottom side), 85 nets.

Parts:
C1, C6, C7, C8, C11, C12, C13, C15, C17, C19, C21, C22, C23, C24, C25, C26, C27, C29, C30, C31, C33, C35, C36, C37, C38, C39, C40, C41, C43, C44, C45, C47, C49, C50, C51, C52, C53, C54, C55, C57, C58, C59, C61, C63, C64, C65, C66, C67, C68, C69, C71, C72, C73, C75: 0.1uF; C_0402_1005Metric
C2: 1uF; C_0402_1005Metric
C3, C4, C5, C14, C16, C18: 10uF; C_0805_2012Metric
C9, C10: 10pF; C_0805_2012Metric
C20: 1uF; C_0805_2012Metric
C28, C32, C42, C46, C56, C60, C70, C74: 10uF; C_0402_1005Metric
C34, C48, C62, C76: 0.01u; C_0402_1005Metric
D1, D2: LED_PWR; LED_0805_2012Metric
D3, D4, D5, D6: CDBU0520/MBR0520LT1G; D_SOD-523
H1, H2, H3, H4: MountingHole_Pad; MountingHole_3.2mm_M3_Pad_Via
J1, J2: 8P8C_Shielded; RJ45_Amphenol_RJHSE5380
J3: I2C; PinHeader_1x04_P2.54mm_Vertical
J4: USB_B_Micro; USB_Micro-B_Amphenol_10103594-0001LF_Horizontal
J5: SWD; PinHeader_2x05_P1.00mm_Vertical
J6: PWR_IN; JST_VH_B2P-VH-B_1x02_P3.96mm_Vertical
JP1: RS485-Term; PinHeader_1x02_P2.54mm_Vertical
L1, L2: FB; L_0805_2012Metric
R1, R2, R3, R4, R5, R7, R9, R10, R13, R14, R15, R16, R17, R26, R33, R34, R37, R38, R41, R42, R45, R46: 4k7; R_0402_1005Metric
R6, R25: 120R; R_0402_1005Metric
R8: OMIT; R_0603_1608Metric_Pad1.05x0.95mm_HandSolder
R11: 10k; R_0402_1005Metric
R12: 0R; SolderJumper-2_P1.3mm_Open_TrianglePad1.0x1.5mm
R18: 196k; R_0402_1005Metric
R19, R20: 8k; R_0402_1005Metric
R21, R22, R23: 110k; R_0402_1005Metric
R24, R30: 1k; R_0402_1005Metric
R27, R28, R29: 250k; R_0402_1005Metric
R31, R32, R35, R36, R39, R40, R43, R44: 100R; R_0402_1005Metric
S1: JS202011SCQN; Switch_Slide_JS202011SCQN
SW1: B3U-1000P; SW_SPST_B3U-1000P-B
TP1: VBUS; TestPoint_Pad_D1.0mm
U1: ISL83488/ISL83490; SOIC-8_3.9x4.9mm_P1.27mm
U2: ATSAMD21E; QFN-32-1EP_5x5mm
U3, U4, U5: TPS77801_HTSSOP20; HTSSOP-20-1EP_4.4x6.5mm_P0.65mm_EP3.4x6.5mm_ThermalVias
U6, U7, U8, U9: iCE40HX8K-BG121(121-Ball_caBGA); BGA-121_11x11_9.0x9.0mm
X1, X2, X3, X4: CB3LV-3I-16M0000; Oscillator_SMD_Abracon_ASV-4Pin_7.0x5.1mm
Y1: 16MHz; Crystal_SMD_Abracon_ABM3B-4Pin_5.0x3.2mm

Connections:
+1V2: R31.2, R32.2, R35.2, R36.2, R39.2, R40.2, R43.2, R44.2
+1V2_0: C16.1, C17.1, C21.2, C24.2, C26.2, C30.2, C35.2, C38.2, C40.2, C44.2, R20.1, R28.1, U4.13, U4.14, U6.D4, U6.D8, U6.H4, U6.H8, U7.D4, U7.D8, U7.H4, U7.H8
+1V2_1: C18.1, C19.1, C49.2, C52.2, C54.2, C58.2, C63.2, C66.2, C68.2, C72.2, R19.1, R29.1, U5.13, U5.14, U8.D4, U8.D8, U8.H4, U8.H8, U9.D4, U9.D8, U9.H4, U9.H8
+3V3: C1.1, C7.2, C14.1, C15.1, C22.2, C23.2, C25.2, C27.2, C31.2, C34.2, C36.2, C37.2, C39.2, C41.2, C45.2, C48.2, C50.2, C51.2, C53.2, C55.2, C59.2, C62.2, C64.2, C65.2, C67.2, C69.2, C73.2, C76.2, D3.2, D4.2, D5.2, D6.2, J3.3, L2.2, R1.2, R2.2, R3.2, R4.2, R5.2, R9.1, R10.1, R11.2, R12.2, R13.2, R14.2, R18.1, R25.1, R26.1, R27.1, R33.1, R37.1, R41.1, R45.1, U1.1, U2.30, U3.13, U3.14, U6.D6, U6.E4, U6.F8, U6.G4, U6.H6, U6.L11, U7.D6, U7.E4, U7.F8, U7.G4, U7.H6, U7.L11, U8.D6, U8.E4, U8.F8, U8.G4, U8.H6, U8.L11, U9.D6, U9.E4, U9.F8, U9.G4, U9.H6, U9.L11, X1.1, X1.4, X2.1, X2.4, X3.1, X3.4, X4.1, X4.4
/CRESET_B_0: R1.1, U2.1, U6.L9
/CRESET_B_1: R2.1, U2.2, U7.L9
/CRESET_B_2: R3.1, U2.3, U8.L9
/CRESET_B_3: R4.1, U2.4, U9.L9
/FIFO_0_1: U6.G11, U7.G1
/FIFO_1_2: U7.G11, U8.G1
/FIFO_2_3: U8.G11, U9.G1
/I2C_SCL: J3.2, R10.2, U2.12
/I2C_SDA: J3.1, R9.2, U2.11
/ICE40HX8K-BG121_0/CLK: U6.B6, X1.3
/ICE40HX8K-BG121_0/GNDPLL0: C28.2, C29.2, U6.L6
/ICE40HX8K-BG121_0/GNDPLL1: C32.2, C33.2, U6.C5
/ICE40HX8K-BG121_0/SPI_SS_B: R34.2, U6.K10
/ICE40HX8K-BG121_0/VCCPLL0: C28.1, C29.1, R31.1, U6.J6
/ICE40HX8K-BG121_0/VCCPLL1: C32.1, C33.1, R32.1, U6.C6
/ICE40HX8K-BG121_0/VPP_2V5: D3.1, U6.C10
/ICE40HX8K-BG121_1/CLK: U7.B6, X2.3
/ICE40HX8K-BG121_1/GNDPLL0: C42.2, C43.2, U7.L6
/ICE40HX8K-BG121_1/GNDPLL1: C46.2, C47.2, U7.C5
/ICE40HX8K-BG121_1/SPI_SS_B: R38.2, U7.K10
/ICE40HX8K-BG121_1/VCCPLL0: C42.1, C43.1, R35.1, U7.J6
/ICE40HX8K-BG121_1/VCCPLL1: C46.1, C47.1, R36.1, U7.C6
/ICE40HX8K-BG121_1/VPP_2V5: D4.1, U7.C10
/ICE40HX8K-BG121_2/CLK: U8.B6, X3.3
/ICE40HX8K-BG121_2/GNDPLL0: C56.2, C57.2, U8.L6
/ICE40HX8K-BG121_2/GNDPLL1: C60.2, C61.2, U8.C5
/ICE40HX8K-BG121_2/SPI_SS_B: R42.2, U8.K10
/ICE40HX8K-BG121_2/VCCPLL0: C56.1, C57.1, R39.1, U8.J6
/ICE40HX8K-BG121_2/VCCPLL1: C60.1, C61.1, R40.1, U8.C6
/ICE40HX8K-BG121_2/VPP_2V5: D5.1, U8.C10
/ICE40HX8K-BG121_3/CLK: U9.B6, X4.3
/ICE40HX8K-BG121_3/GNDPLL0: C70.2, C71.2, U9.L6
/ICE40HX8K-BG121_3/GNDPLL1: C74.2, C75.2, U9.C5
/ICE40HX8K-BG121_3/SPI_SS_B: R46.2, U9.K10
/ICE40HX8K-BG121_3/VCCPLL0: C70.1, C71.1, R43.1, U9.J6
/ICE40HX8K-BG121_3/VCCPLL1: C74.1, C75.1, R44.1, U9.C6
/ICE40HX8K-BG121_3/VPP_2V5: D6.1, U9.C10
/MISO: R16.2, U2.20, U9.G11
/MOSI: R15.2, U2.17, U6.G1, U6.J9, U7.J9, U8.J9, U9.J9
/READY: R7.2, U2.25, U9.F10
/READY_0: R5.1, R8.2, U6.F3
/READY_0_1: U6.F10, U7.F3
/READY_1_2: U7.F10, U8.F3
/READY_2_3: U8.F10, U9.F3
/RX: U1.2, U2.5
/RX+: J1.1, J2.1, JP1.2, U1.8
/RX-: J1.2, J2.2, R6.2, U1.7
/SCK: R17.2, U2.19, U6.L10, U7.L10, U8.L10, U9.L10
/SWD_CLK: J5.4, R11.1, U2.31
/SWD_IO: J5.2, U2.32
/TX: U1.3, U2.6
/TX+: J1.3, J2.3, U1.5
/TX-: J1.6, J2.6, U1.6
/USB_D+: J4.3, U2.21
/USB_D-: J4.2, U2.22
/VDDANA: C8.2, L2.1, U2.9
/VDDCORE: C2.2, C6.2, U2.29
/VPWR: J6.2, S1.2, S1.5
/XIN: C9.1, U2.15, Y1.1
/XOUT: C10.1, U2.16, Y1.3
/~GS: R14.1, U2.27, U6.K6, U7.K6, U8.K6, U9.K6
/~RESET: C20.1, J5.10, R26.2, R30.1, U2.26
/~WE: R13.1, U2.18, U6.L5, U7.L5, U8.L5, U9.L5
GND: C1.2, C2.1, C3.2, C4.2, C5.2, C6.1, C7.1, C8.1, C9.2, C10.2, C11.2, C12.2, C13.2, C14.2, C15.2, C16.2, C17.2, C18.2, C19.2, C20.2, C21.1, C22.1, C23.1, C24.1, C25.1, C26.1, C27.1, C30.1, C31.1, C34.1, C35.1, C36.1, C37.1, C38.1, C39.1, C40.1, C41.1, C44.1, C45.1, C48.1, C49.1, C50.1, C51.1, C52.1, C53.1, C54.1, C55.1, C58.1, C59.1, C62.1, C63.1, C64.1, C65.1, C66.1, C67.1, C68.1, C69.1, C72.1, C73.1, C76.1, D1.1, D2.1, H1.1, H2.1, H3.1, H4.1, J3.4, J4.5, J5.3, J5.5, J5.7, J5.9, J6.1, R7.1, R8.1, R15.1, R16.1, R17.1, R21.2, R22.2, R23.2, R34.1, R38.1, R42.1, R46.1, SW1.2, U1.4, U2.10, U2.28, U3.1, U3.2, U3.3, U3.5, U3.9, U3.10, U3.11, U3.12, U3.19, U3.20, U3.21, U4.1, U4.2, U4.3, U4.9, U4.10, U4.11, U4.12, U4.19, U4.20, U4.21, U5.1, U5.2, U5.3, U5.9, U5.10, U5.11, U5.12, U5.19, U5.20, U5.21, U6.E5, U6.E6, U6.E7, U6.F5, U6.F6, U6.F7, U6.G5, U6.G6, U6.G7, U6.H5, U7.E5, U7.E6, U7.E7, U7.F5, U7.F6, U7.F7, U7.G5, U7.G6, U7.G7, U7.H5, U8.E5, U8.E6, U8.E7, U8.F5, U8.F6, U8.F7, U8.G5, U8.G6, U8.G7, U8.H5, U9.E5, U9.E6, U9.E7, U9.F5, U9.F6, U9.F7, U9.G5, U9.G6, U9.G7, U9.H5, X1.2, X2.2, X3.2, X4.2, Y1.2, Y1.4
unnamed: D1.2, R24.2
unnamed: D2.2, R25.2
unnamed: J4.1, TP1.1
unnamed: J5.1, R12.1
unnamed: JP1.1, R6.1
unnamed: L1.1, S1.3, S1.6
unnamed: R18.2, R21.1, U3.15
unnamed: R19.2, R22.1, U5.15
unnamed: R20.2, R23.1, U4.15
unnamed: R30.2, SW1.1
unnamed: R33.2, U6.K8
unnamed: R37.2, U7.K8
unnamed: R41.2, U8.K8
unnamed: R45.2, U9.K8
PG_0: R27.2, U3.16, U4.5
PG_1: R28.2, U4.16, U5.5
VCC: C3.1, C4.1, C5.1, C11.1, C12.1, C13.1, L1.2, R24.1, U3.6, U3.7, U4.6, U4.7, U5.6, U5.7
